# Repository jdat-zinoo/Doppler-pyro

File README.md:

# Doppler-tiny
Atmega pyro eject control with supercap and doppler transmitter.

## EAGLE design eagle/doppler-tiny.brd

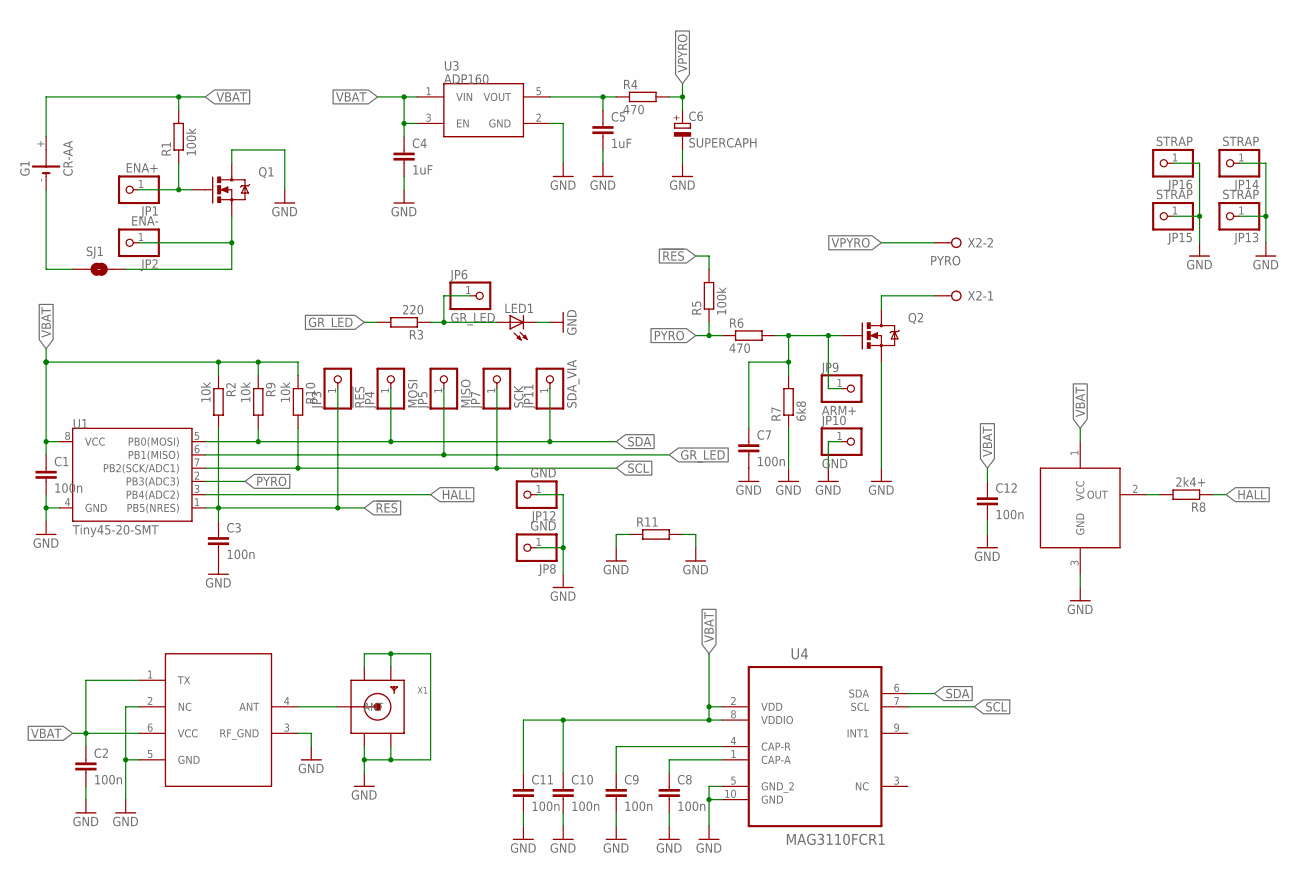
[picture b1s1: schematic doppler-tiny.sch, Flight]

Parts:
C1, C2, C3, C7, C8, C9, C10, C11, C12: 100n; C0603
C4, C5: 1uF; C0603
C6: SUPERCAPH; E3,5-8-HOR
G1: CR-AA; CRAA
JP1: ENA+; 1X01
JP2: ENA-; 1X01
JP3: !RES; 1X01
JP4: MOSI; 1X01
JP5: MISO; 1X01
JP6: GR_LED; 1X01
JP7: SCK; 1X01
JP8, JP10, JP12: GND; 1X01
JP9: ARM+; 1X01
JP11: SDA_VIA; 1X01
JP13, JP14, JP15, JP16: STRAP; 1X01
LED1: LEDCHIPLED_0805; CHIPLED_0805
Q1, Q2: MOSFET-NCHANNELBSS123LT1G; SOT23-3
R1, R5: 100k; R0603
R2, R9, R10: 10k; R0603
R3: 220; R0603
R4, R6: 470; R0603
R7: 6k8; R0603
R8: 2k4+; R0603
R11: R-EU_R1206; R1206
SJ1: JUMPER-PAD-2-NO; PAD-JUMPER-2-NO_NO_SILK
U1: Tiny45-20-SMT; SO08-EIAJ
U2: AUREL-TX-FM-MID
U3: ADP160; SOT23-5; FARNELL 2510377
U4: MAG3110FCR1; DFN200X200X90-10N
U5: SS39ET; SOT23
X1: SMACONNECTOR_EDGE; SMA_EDGELAUNCH
X2: PYRO; W237-132

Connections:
!RES: C3.1, JP3.1, R2.2, R5.2, U1.1 (PB5(NRES))
GND: C1.2, C2.2, C3.2, C4.2, C5.2, C6.-, C7.2, C8.2, C9.2, C10.2, C11.2, C12.2, JP8.1, JP10.1, JP12.1, JP13.1, JP14.1, JP15.1, JP16.1, LED1.C, Q1.3 (D), Q2.2 (S), R7.1, R11.1, R11.2, U1.4 (GND), U2.2 (NC), U2.3 (RF_GND), U2.5 (GND), U3.2 (GND), U4.5 (GND_2), U4.10 (GND), U5.3 (GND), X1.GND@1 (GND4), X1.GND@3 (GND2), X1.GND@4 (GND1)
GND3: X1.GND@2 (GND3)
GR_LED: JP5.1, R3.2, U1.6 (PB1(MISO))
HALL: R8.1, U1.3 (PB4(ADC2))
unnamed: C5.1, R4.1, U3.5 (VOUT)
unnamed: JP1.1, Q1.1 (G), R1.1
unnamed: JP2.1, Q1.2 (S), SJ1.2
unnamed: C8.1, U4.1 (CAP-A)
unnamed: U2.4 (ANT), X1.P (ANT)
unnamed: C9.1, U4.4 (CAP-R)
unnamed: R8.2, U5.2 (OUT)
unnamed: G1.-, SJ1.1
unnamed: C7.1, JP9.1, Q2.1 (G), R6.2, R7.2
unnamed: JP6.1, LED1.A, R3.1
unnamed: Q2.3 (D), X2.1
PYRO: R5.1, R6.1, U1.2 (PB3(ADC3))
SCL: JP7.1, R10.2, U1.7 (PB2(SCK/ADC1)), U4.7 (SCL)
SDA: JP4.1, JP11.1, R9.2, U1.5 (PB0(MOSI)), U4.6 (SDA)
VBAT: C1.1, C2.1, C4.1, C10.1, C11.1, C12.1, G1.+, R1.2, R2.1, R9.1, R10.1, U1.8 (VCC), U2.1 (TX), U2.6 (VCC), U3.1 (VIN), U3.3 (EN), U4.2 (VDD), U4.8 (VDDIO), U5.1 (VCC)
VPYRO: C6.+, R4.2, X2.2

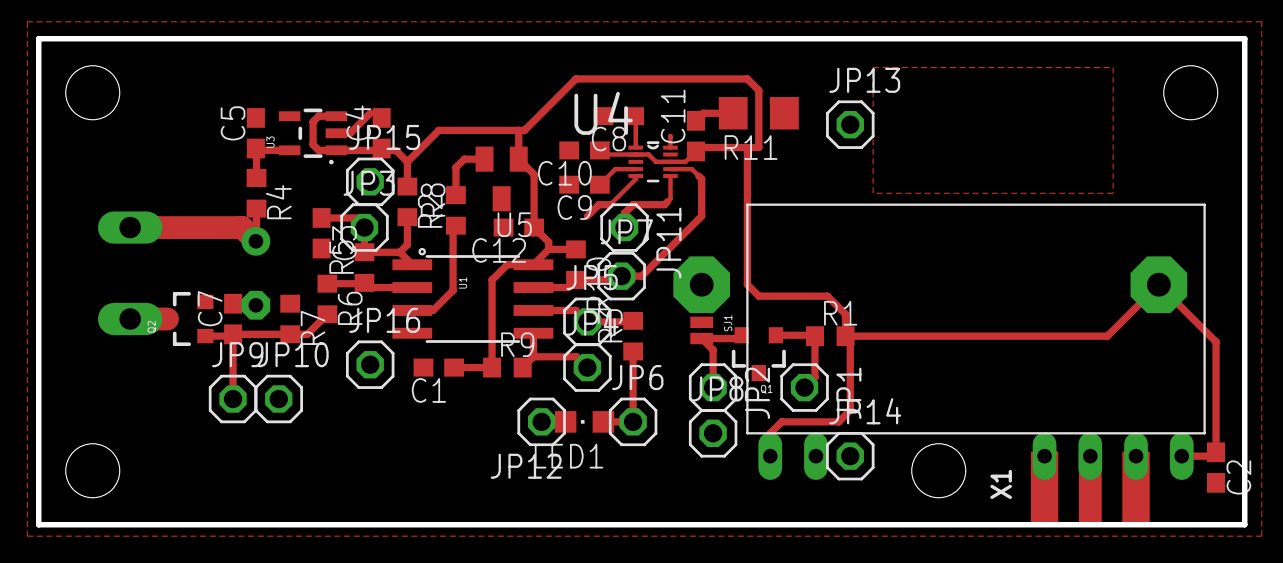
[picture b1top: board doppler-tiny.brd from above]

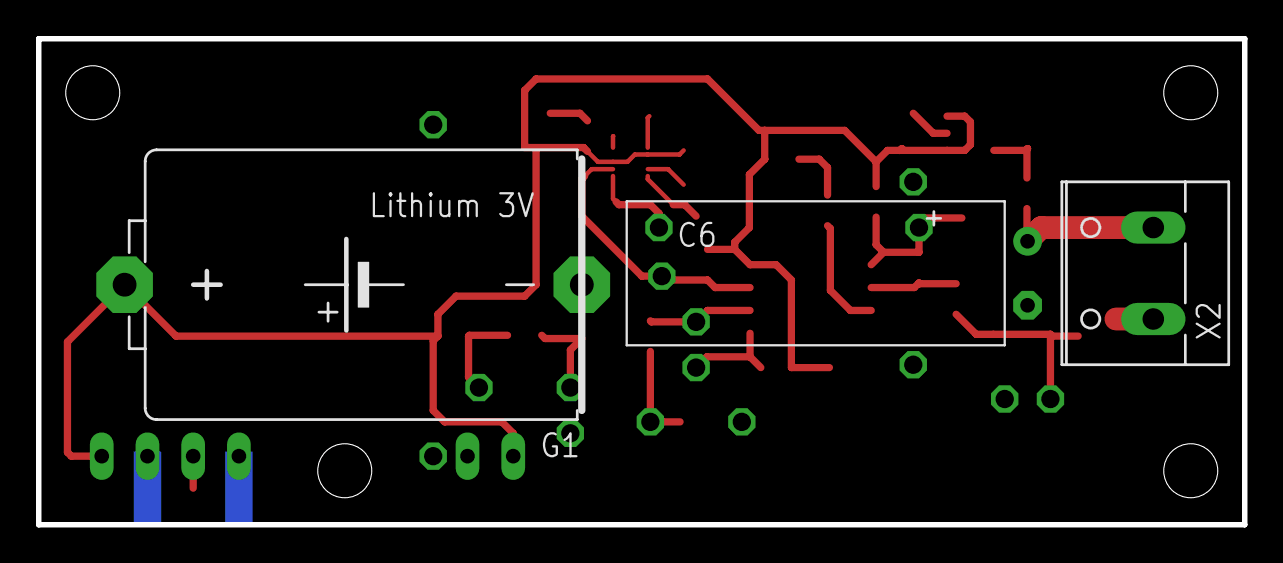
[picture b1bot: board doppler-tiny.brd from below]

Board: 2 copper layers, 67.0 x 27.0 mm, 51 parts (3 on the bottom side), 20 nets.

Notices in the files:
parts and their libraries:
SparkFun-DiscreteSemi: Licensing: Creative Commons ShareAlike 4.0 International - https://creativecommons.org/licenses/by-sa/4.0
